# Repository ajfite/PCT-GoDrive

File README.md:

# PC Transporter GoDrive

A clone of the original Applied Engineering Transdrive adapter that allows
you to connect an Apple II PC Transporter to a standard DOS Drive.

At this time it has only been tested with Gotek Floppy Emulators but it
should allow you to use any DOS PC Drive of the era.

## BOM

The DigiKey part number reflect my most recent order - you can substitute as you see fit.

| Schematic Part | Part                       | Total Quantity | Manufacturer Part Number | DigiKey Part Number | Notes |
|----------------|----------------------------|----------------|--------------------------|---------------------|-------|
| U1             | 74LS138/1                  | 1              | TI SN74LS138N            | 296-1639-5-ND       |       |
| U2             | 7407N                      | 1              | TI SN7407N               | 296-1436-ND         |       |
| R1, R2, R3, R4 | 2.7K Resistor              | 4              | Stackpole RSMF2JT2K70    | RSMF2JT2K70CT-ND    | Any 2.7k commodity resistor will work, the pad is sized perfectly for the noted part but you definitely can use a smaller cheaper resistor. The large resistors where an aesthetic choice. |
| C1, C2         | 0.1uF Capacitor            | 2              | Nichicon UKL1H0R1MDDANA  | 493-15375-ND        |       |
| J1, J2         | 34 position keyed header   | Up to 2        | On Shore Tech 302-S341   | ED10528-ND          | This connector is optional, depends on how you want to connect your floppy drive to the board |

Total BOM cost for parts only at time of purchasing (June 13, 2023) was $11.81.

Unfortunately the DB-19 connector for the Apple II interface is not easily sourced, so it is not included here.

## License

This work is licensed under a [Creative Commons Attribution-ShareAlike 4.0 International License](http://creativecommons.org/licenses/by-sa/4.0/).

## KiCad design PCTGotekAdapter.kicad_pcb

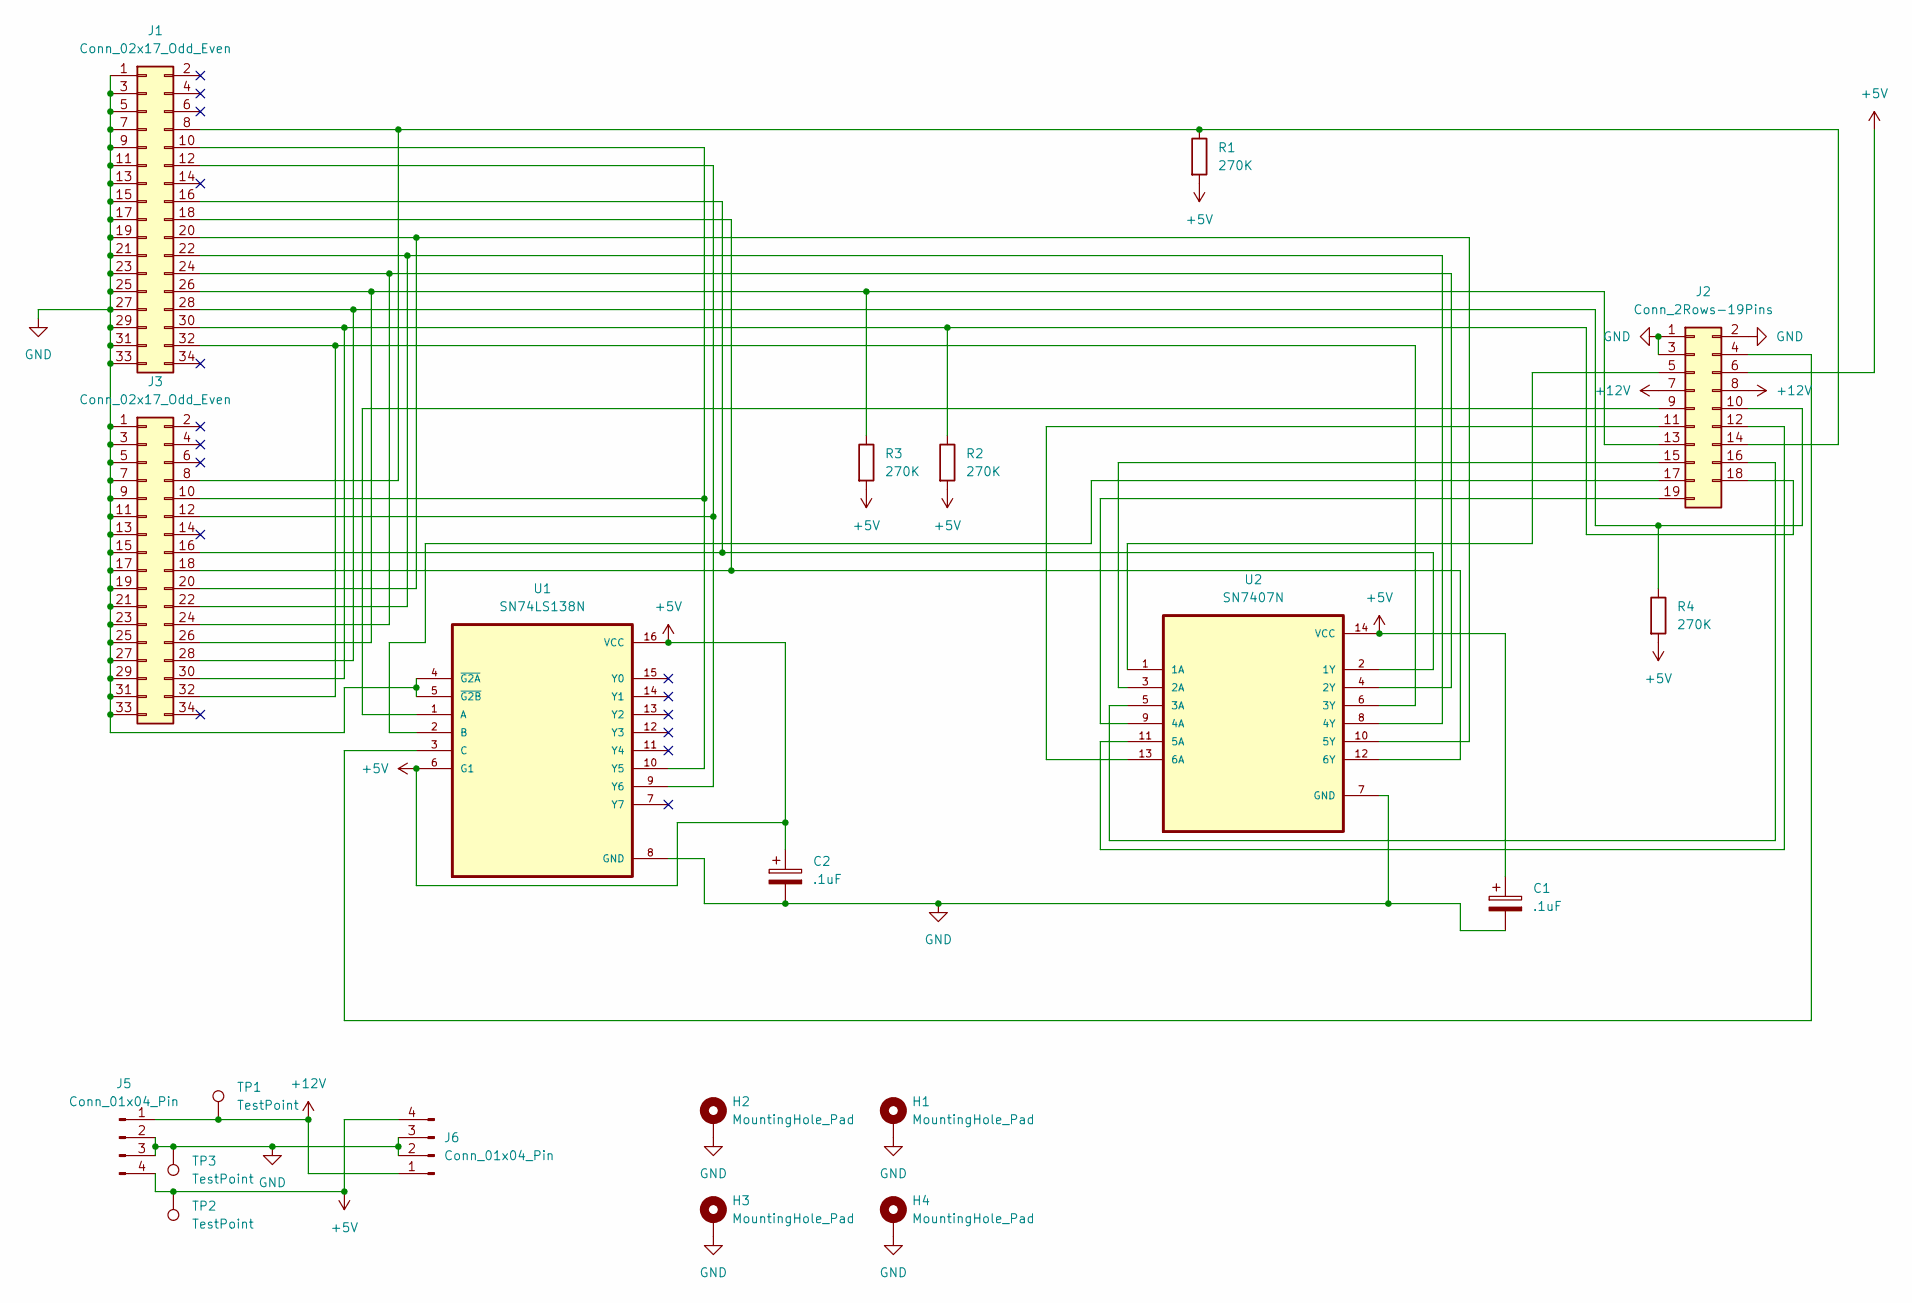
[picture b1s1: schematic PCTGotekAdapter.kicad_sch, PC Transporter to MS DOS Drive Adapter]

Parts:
C1, C2: .1uF; CP_Radial_D5.0mm_P2.00mm
H1, H2, H3, H4: MountingHole_Pad; MountingHole_3.2mm_M3_Pad_Via
J1, J3: Conn_02x17_Odd_Even; PinHeader_2x17_P2.54mm_Vertical
J2: Conn_2Rows-19Pins; PinHeader_2x10_P2.54mm_Vertical
J5, J6: Conn_01x04_Pin; PinSocket_1x04_P2.54mm_Vertical
R1, R2, R3, R4: 270K; R_Axial_DIN0414_L11.9mm_D4.5mm_P15.24mm_Horizontal
TP1, TP2, TP3: TestPoint; TestPoint_Pad_2.5x2.5mm
U1: SN74LS138N; DIP794W45P254L1969H508Q16
U2: SN7407N; DIP794W45P254L1969H508Q14

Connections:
+5V: C1.1, C2.1, J2.6, J5.4, J6.4, R1.2, R2.2, R3.2, R4.2, TP2.1, U1.6 (G1), U1.16 (VCC), U2.14 (VCC)
+12V: J2.7, J2.8, J5.1, J6.1, TP1.1
GND: C1.2, C2.2, H1.1, H2.1, H3.1, H4.1, J1.1, J1.3, J1.5, J1.7, J1.9, J1.11, J1.13, J1.15, J1.17, J1.19, J1.21, J1.23, J1.25, J1.27, J1.29, J1.31, J1.33, J2.1, J2.2, J2.3, J3.1, J3.3, J3.5, J3.7, J3.9, J3.11, J3.13, J3.15, J3.17, J3.19, J3.21, J3.23, J3.25, J3.27, J3.29, J3.31, J3.33, J5.2, J5.3, J6.2, J6.3, TP3.1, U1.4 (~G2A), U1.5 (~G2B), U1.8 (GND), U2.7 (GND)
unnamed: J1.8, J2.14, J3.8, R1.1
unnamed: J1.10, J3.10, U1.10 (Y5)
unnamed: J1.12, J3.12, U1.9 (Y6)
unnamed: J1.16, J3.16, U2.2 (1Y)
unnamed: J1.18, J3.18, U2.12 (6Y)
unnamed: J1.20, J3.20, U2.10 (5Y)
unnamed: J1.22, J3.22, U2.8 (4Y)
unnamed: J1.24, J3.24, U2.4 (2Y)
unnamed: J1.26, J2.13, J3.26, R3.1
unnamed: J1.28, J2.10, J3.28, R4.1
unnamed: J1.30, J2.18, J3.30, R2.1
unnamed: J1.32, J3.32, U2.6 (3Y)
unnamed: J2.4, U1.3 (C)
unnamed: J2.5, U2.1 (1A)
unnamed: J2.9, U1.1 (A)
unnamed: J2.11, U2.13 (6A)
unnamed: J2.12, U2.11 (5A)
unnamed: J2.15, U2.3 (2A)
unnamed: J2.16, U2.5 (3A)
unnamed: J2.17, U1.2 (B)
unnamed: J2.19, U2.9 (4A)

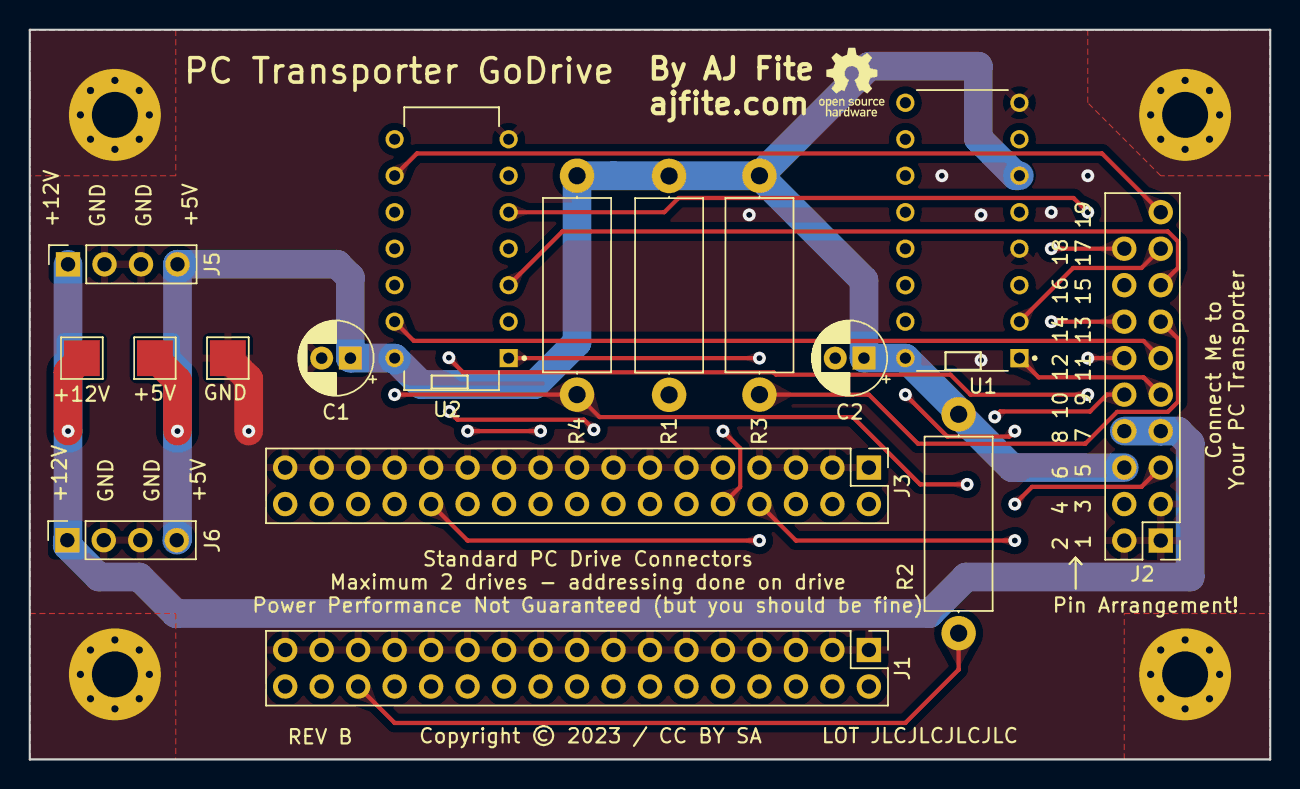
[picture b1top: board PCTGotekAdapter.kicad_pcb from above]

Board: 4 copper layers, 86.4 x 50.8 mm, 20 parts (0 on the bottom side), 24 nets.

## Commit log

2023-06-06 REV A commit
2023-06-22 First pass at REV B
2023-06-22 Remove extraneous connector from schematic
    Also some silkscreen and path tweaks
2023-07-15 Additional updates to the PCB and silk
    This will be ready for printing extremely soon
2023-07-28 Silkscreen and routing updates, schematic fixes
    Also ignored .zip files
2023-07-28 Changes to schematic info
2024-06-27 Correct an error on the schematic
    Resistors were listed as 270K, they should be 2.7K
2024-06-27 Add the BOM to the README
2024-06-27 Ignore some garbage KiCAD makes
2024-06-27 Rev B production files
2024-06-27 Adding more KiCAD autosave stuff

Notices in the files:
PCTGotekAdapter.kicad_pcb:
Copyright ©️ 2023 / CC BY SA
